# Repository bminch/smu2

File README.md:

# smu2
USB Source Measure Unit Design Files and Source Code

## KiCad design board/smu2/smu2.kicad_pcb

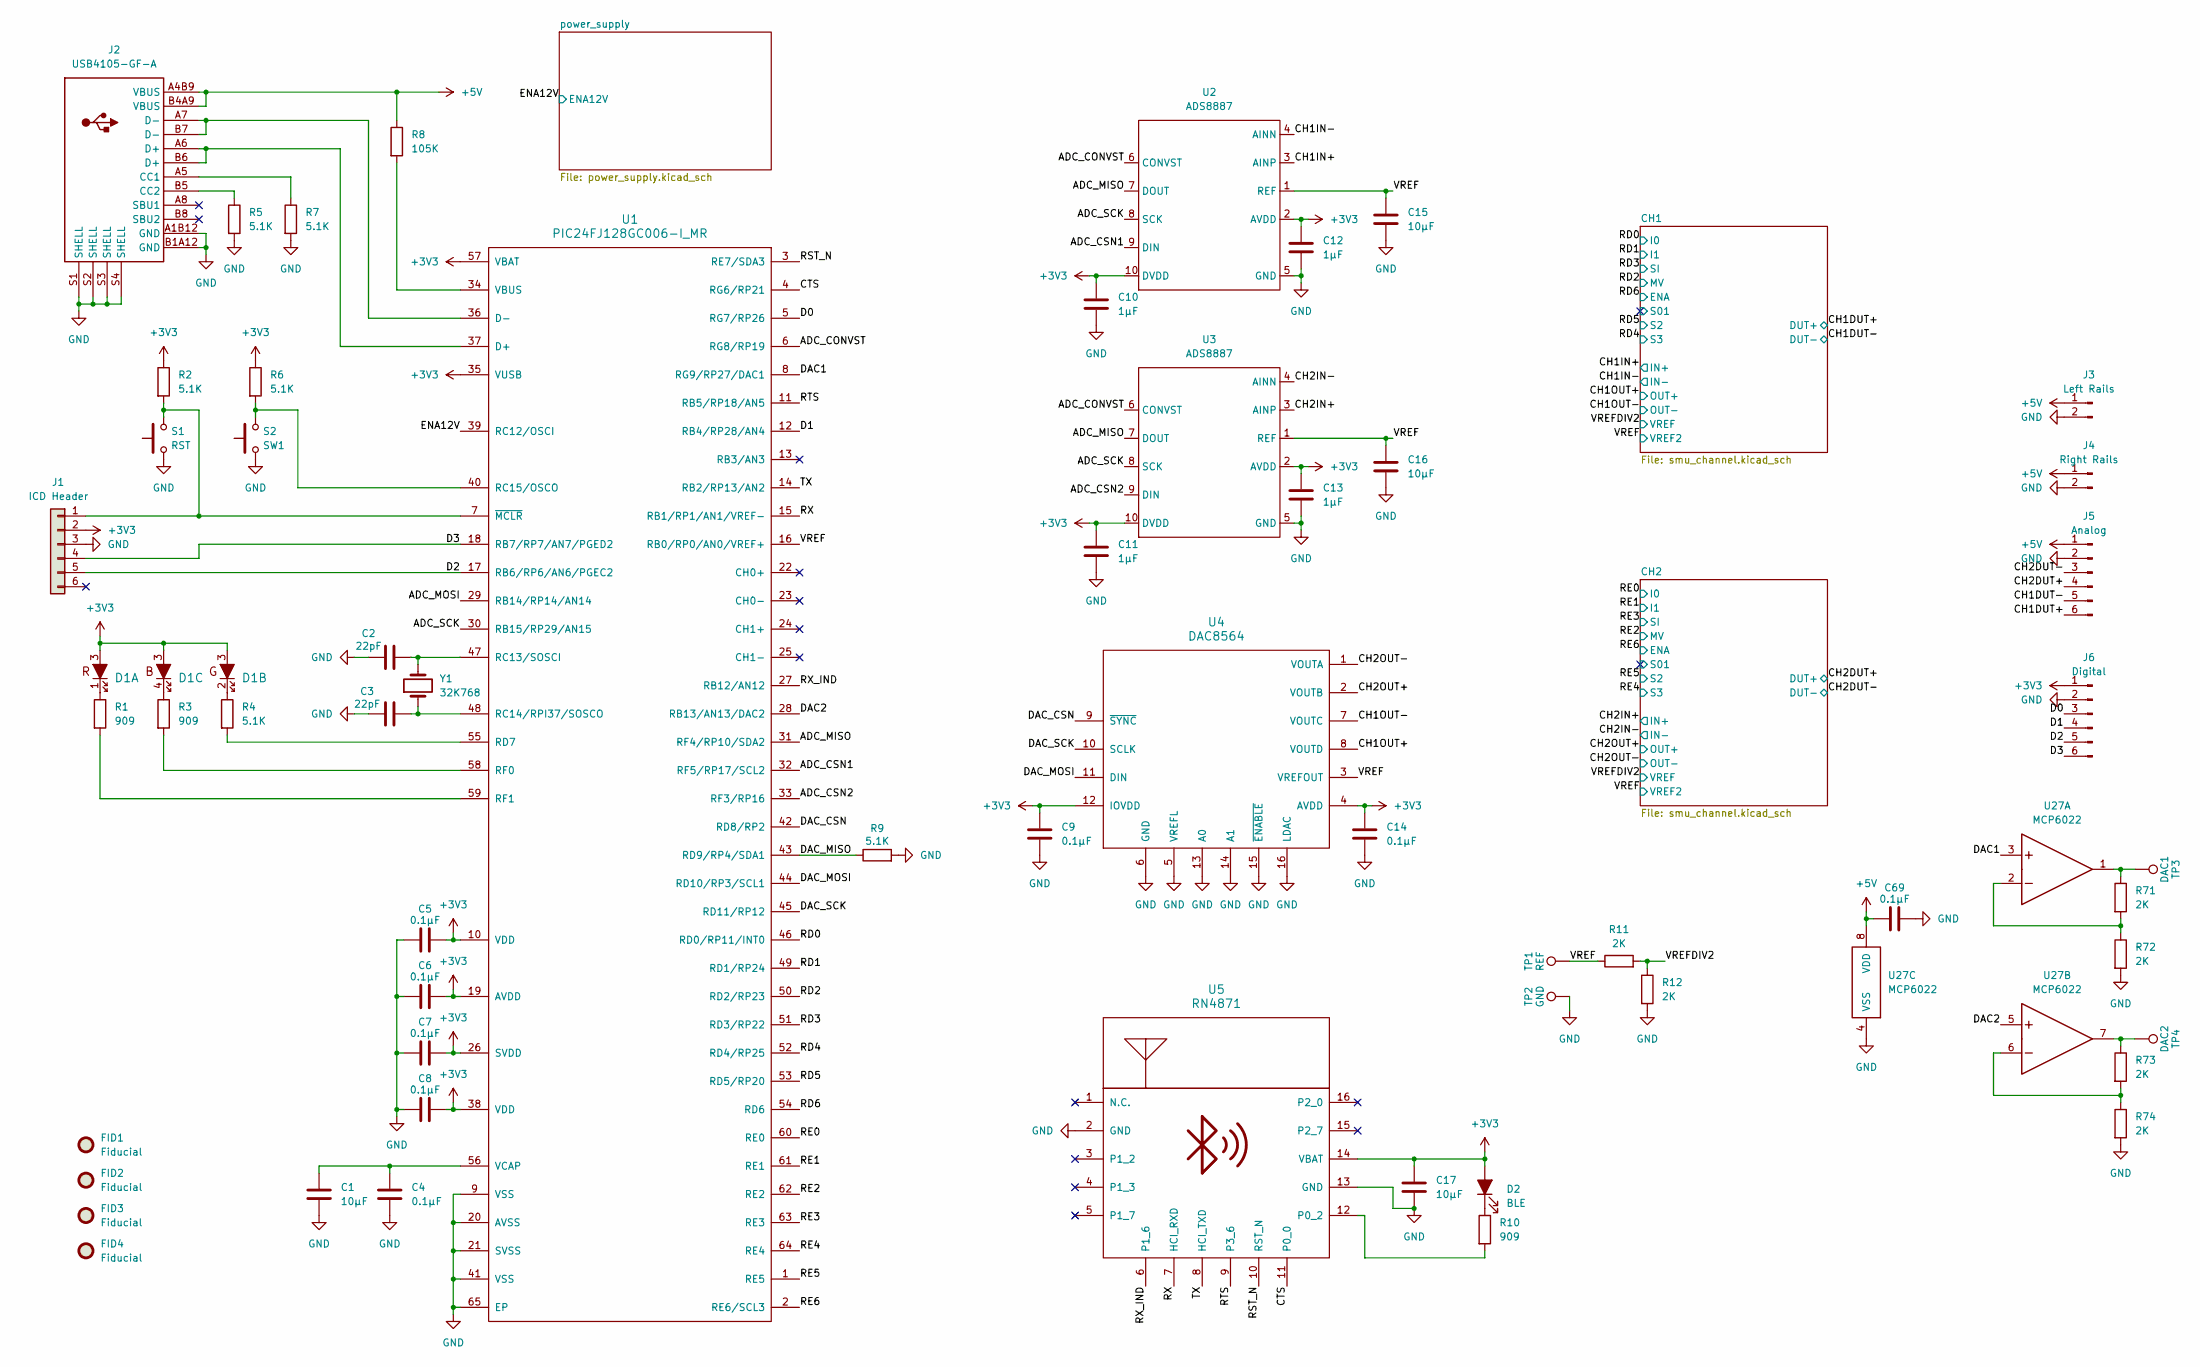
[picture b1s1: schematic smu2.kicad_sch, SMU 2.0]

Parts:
C1, C15, C16, C17: 10µF; C_0603_1608Metric
C2, C3: 22pF; C_0603_1608Metric
C4, C5, C6, C7, C8, C9, C14, C69: 0.1µF; C_0603_1608Metric
C10, C11, C12, C13: 1µF; C_0603_1608Metric
D1: IN-S85TATRGB_ALT; IN-S85TATRGB
D2: BLE; LED_0805_2012Metric
FID1, FID2, FID3, FID4: Fiducial; Fiducial_1mm_Mask2mm
J1: ICD Header; ICD3_header
J2: USB4105-GF-A
J3: Left Rails; PinHeader_1x02_P2.54mm_Vertical
J4: Right Rails; PinHeader_1x02_P2.54mm_Vertical
J5: Analog; PinHeader_1x06_P2.54mm_Vertical
J6: Digital; PinHeader_1x06_P2.54mm_Vertical
R1, R3, R10: 909; R_0603_1608Metric
R2, R4, R5, R6, R7, R9: 5.1K; R_0603_1608Metric
R8: 105K; R_0603_1608Metric
R11, R12, R71, R72, R73, R74: 2K; R_0603_1608Metric
S1: RST; KXT321LHS
S2: SW1; KXT321LHS
TP1: REF; TestPoint_THTPad_D1.5mm_Drill0.7mm
TP2: GND; TestPoint_THTPad_D1.5mm_Drill0.7mm
TP3: DAC1; TestPoint_THTPad_D1.5mm_Drill0.7mm
TP4: DAC2; TestPoint_THTPad_D1.5mm_Drill0.7mm
U1: PIC24FJ128GC006-I_MR; pic24fj128gc006_1
U2, U3: ADS8887; TSSOP-10_3x3mm_P0.5mm
U4: DAC8564; TSSOP-16_4.4x5mm_P0.65mm
U5: RN4871
U27: MCP6022; TSSOP-8_4.4x3mm_P0.65mm
Y1: 32K768; Crystal_SMD_2012-2Pin_2.0x1.2mm

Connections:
+3V3: C5.2, C6.2, C7.2, C8.2, C9.1, C10.1, C11.1, C12.1, C13.1, C14.1, C17.1, D1.3, D2.2 (A), J1.2, J6.1, R2.1, R6.1, U1.10 (VDD), U1.19 (AVDD), U1.26 (SVDD), U1.35 (VUSB), U1.38 (VDD), U1.57 (VBAT), U2.2 (AVDD), U2.10 (DVDD), U3.2 (AVDD), U3.10 (DVDD), U4.4 (AVDD), U4.12 (IOVDD), U5.14 (VBAT); also elsewhere on the board
+5V: C69.1, J2.A4B9 (VBUS), J2.B4A9 (VBUS), J3.1, J4.1, J5.1, R8.1, U27.8 (VDD); also elsewhere on the board
/ADC_CONVST: U1.6 (RG8/RP19), U2.6 (CONVST), U3.6 (CONVST)
/ADC_CSN1: U1.32 (RF5/RP17/SCL2), U2.9 (DIN)
/ADC_CSN2: U1.33 (RF3/RP16), U3.9 (DIN)
/ADC_MISO: U1.31 (RF4/RP10/SDA2), U2.7 (DOUT), U3.7 (DOUT)
/ADC_MOSI: U1.29 (RB14/RP14/AN14)
/ADC_SCK: U1.30 (RB15/RP29/AN15), U2.8 (SCK), U3.8 (SCK)
/CH1DUT+: J5.6; also elsewhere on the board
/CH1DUT-: J5.5; also elsewhere on the board
/CH1IN+: U2.3 (AINP); also elsewhere on the board
/CH1IN-: U2.4 (AINN); also elsewhere on the board
/CH1OUT+: U4.8 (VOUTD); also elsewhere on the board
/CH1OUT-: U4.7 (VOUTC); also elsewhere on the board
/CH2DUT+: J5.4; also elsewhere on the board
/CH2DUT-: J5.3; also elsewhere on the board
/CH2IN+: U3.3 (AINP); also elsewhere on the board
/CH2IN-: U3.4 (AINN); also elsewhere on the board
/CH2OUT+: U4.2 (VOUTB); also elsewhere on the board
/CH2OUT-: U4.1 (VOUTA); also elsewhere on the board
/CTS: U1.4 (RG6/RP21), U5.11 (P0_0)
/D0: J6.3, U1.5 (RG7/RP26)
/D1: J6.4, U1.12 (RB4/RP28/AN4)
/D2: J1.5, J6.5, U1.17 (RB6/RP6/AN6/PGEC2)
/D3: J1.4, J6.6, U1.18 (RB7/RP7/AN7/PGED2)
/DAC1: U1.8 (RG9/RP27/DAC1), U27.3
/DAC2: U1.28 (RB13/AN13/DAC2), U27.5
/DAC_CSN: U1.42 (RD8/RP2), U4.9 (~SYNC)
/DAC_MISO: R9.1, U1.43 (RD9/RP4/SDA1)
/DAC_MOSI: U1.44 (RD10/RP3/SCL1), U4.11 (DIN)
/DAC_SCK: U1.45 (RD11/RP12), U4.10 (SCLK)
/ENA12V: U1.39 (RC12/OSCI); also elsewhere on the board
/RD0: U1.46 (RD0/RP11/INT0); also elsewhere on the board
/RD1: U1.49 (RD1/RP24); also elsewhere on the board
/RD2: U1.50 (RD2/RP23); also elsewhere on the board
/RD3: U1.51 (RD3/RP22); also elsewhere on the board
/RD4: U1.52 (RD4/RP25)
/RD5: U1.53 (RD5/RP20); also elsewhere on the board
/RD6: U1.54 (RD6); also elsewhere on the board
/RE0: U1.60 (RE0); also elsewhere on the board
/RE1: U1.61 (RE1); also elsewhere on the board
/RE2: U1.62 (RE2); also elsewhere on the board
/RE3: U1.63 (RE3); also elsewhere on the board
/RE4: U1.64 (RE4)
/RE5: U1.1 (RE5); also elsewhere on the board
/RE6: U1.2 (RE6/SCL3); also elsewhere on the board
/RST_N: U1.3 (RE7/SDA3), U5.10 (RST_N)
/RTS: U1.11 (RB5/RP18/AN5), U5.9 (P3_6)
/RX: U1.15 (RB1/RP1/AN1/VREF-), U5.7 (HCI_RXD)
/RX_IND: U1.27 (RB12/AN12), U5.6 (P1_6)
/TX: U1.14 (RB2/RP13/AN2), U5.8 (HCI_TXD)
/VREF: C15.1, C16.1, R11.1, TP1.1, U1.16 (RB0/RP0/AN0/VREF+), U2.1 (REF), U3.1 (REF), U4.3 (VREFOUT); also elsewhere on the board
/VREFDIV2: R11.2, R12.1; also elsewhere on the board
GND: C1.2, C2.1, C3.1, C4.2, C5.1, C6.1, C7.1, C8.1, C9.2, C10.2, C11.2, C12.2, C13.2, C14.2, C15.2, C16.2, C17.2, C69.2, J1.3, J2.A1B12 (GND), J2.B1A12 (GND), J2.S1 (SHELL), J2.S2 (SHELL), J2.S3 (SHELL), J2.S4 (SHELL), J3.2, J4.2, J5.2, J6.2, R5.2, R7.2, R9.2, R12.2, R72.2, R74.2, S1.1, S2.1, TP2.1, U1.9 (VSS), U1.20 (AVSS), U1.21 (SVSS), U1.41 (VSS), U1.65 (EP), U2.5 (GND), U3.5 (GND), U4.5 (VREFL), U4.6 (GND), U4.13 (A0), U4.14 (A1), U4.15 (~ENABLE), U4.16 (LDAC), U5.2 (GND), U5.13 (GND), U27.4 (VSS); also elsewhere on the board
unnamed: D1.1, R1.1
unnamed: D1.2, R4.1
unnamed: D1.4, R3.1
unnamed: D2.1 (K), R10.1
unnamed: J1.1, R2.2, S1.2, U1.7 (~MCLR)
unnamed: J2.A5 (CC1), R7.1
unnamed: J2.B5 (CC2), R5.1
unnamed: R71.1, TP3.1, U27.1
unnamed: R71.2, R72.1, U27.2
unnamed: R73.1, TP4.1, U27.7
unnamed: R73.2, R74.1, U27.6
unnamed: J2.A6 (D+), J2.B6 (D+), U1.37 (D+)
unnamed: J2.A7 (D-), J2.B7 (D-), U1.36 (D-)
unnamed: C2.2, U1.47 (RC13/SOSCI), Y1.2
unnamed: C3.2, U1.48 (RC14/RPI37/SOSCO), Y1.1
unnamed: R6.2, S2.2, U1.40 (RC15/OSCO)
unnamed: R4.2, U1.55 (RD7)
unnamed: R3.2, U1.58 (RF0)
unnamed: R1.2, U1.59 (RF1)
unnamed: R8.2, U1.34 (VBUS)
unnamed: C1.1, C4.1, U1.56 (VCAP)
unnamed: R10.2, U5.12 (P0_2)

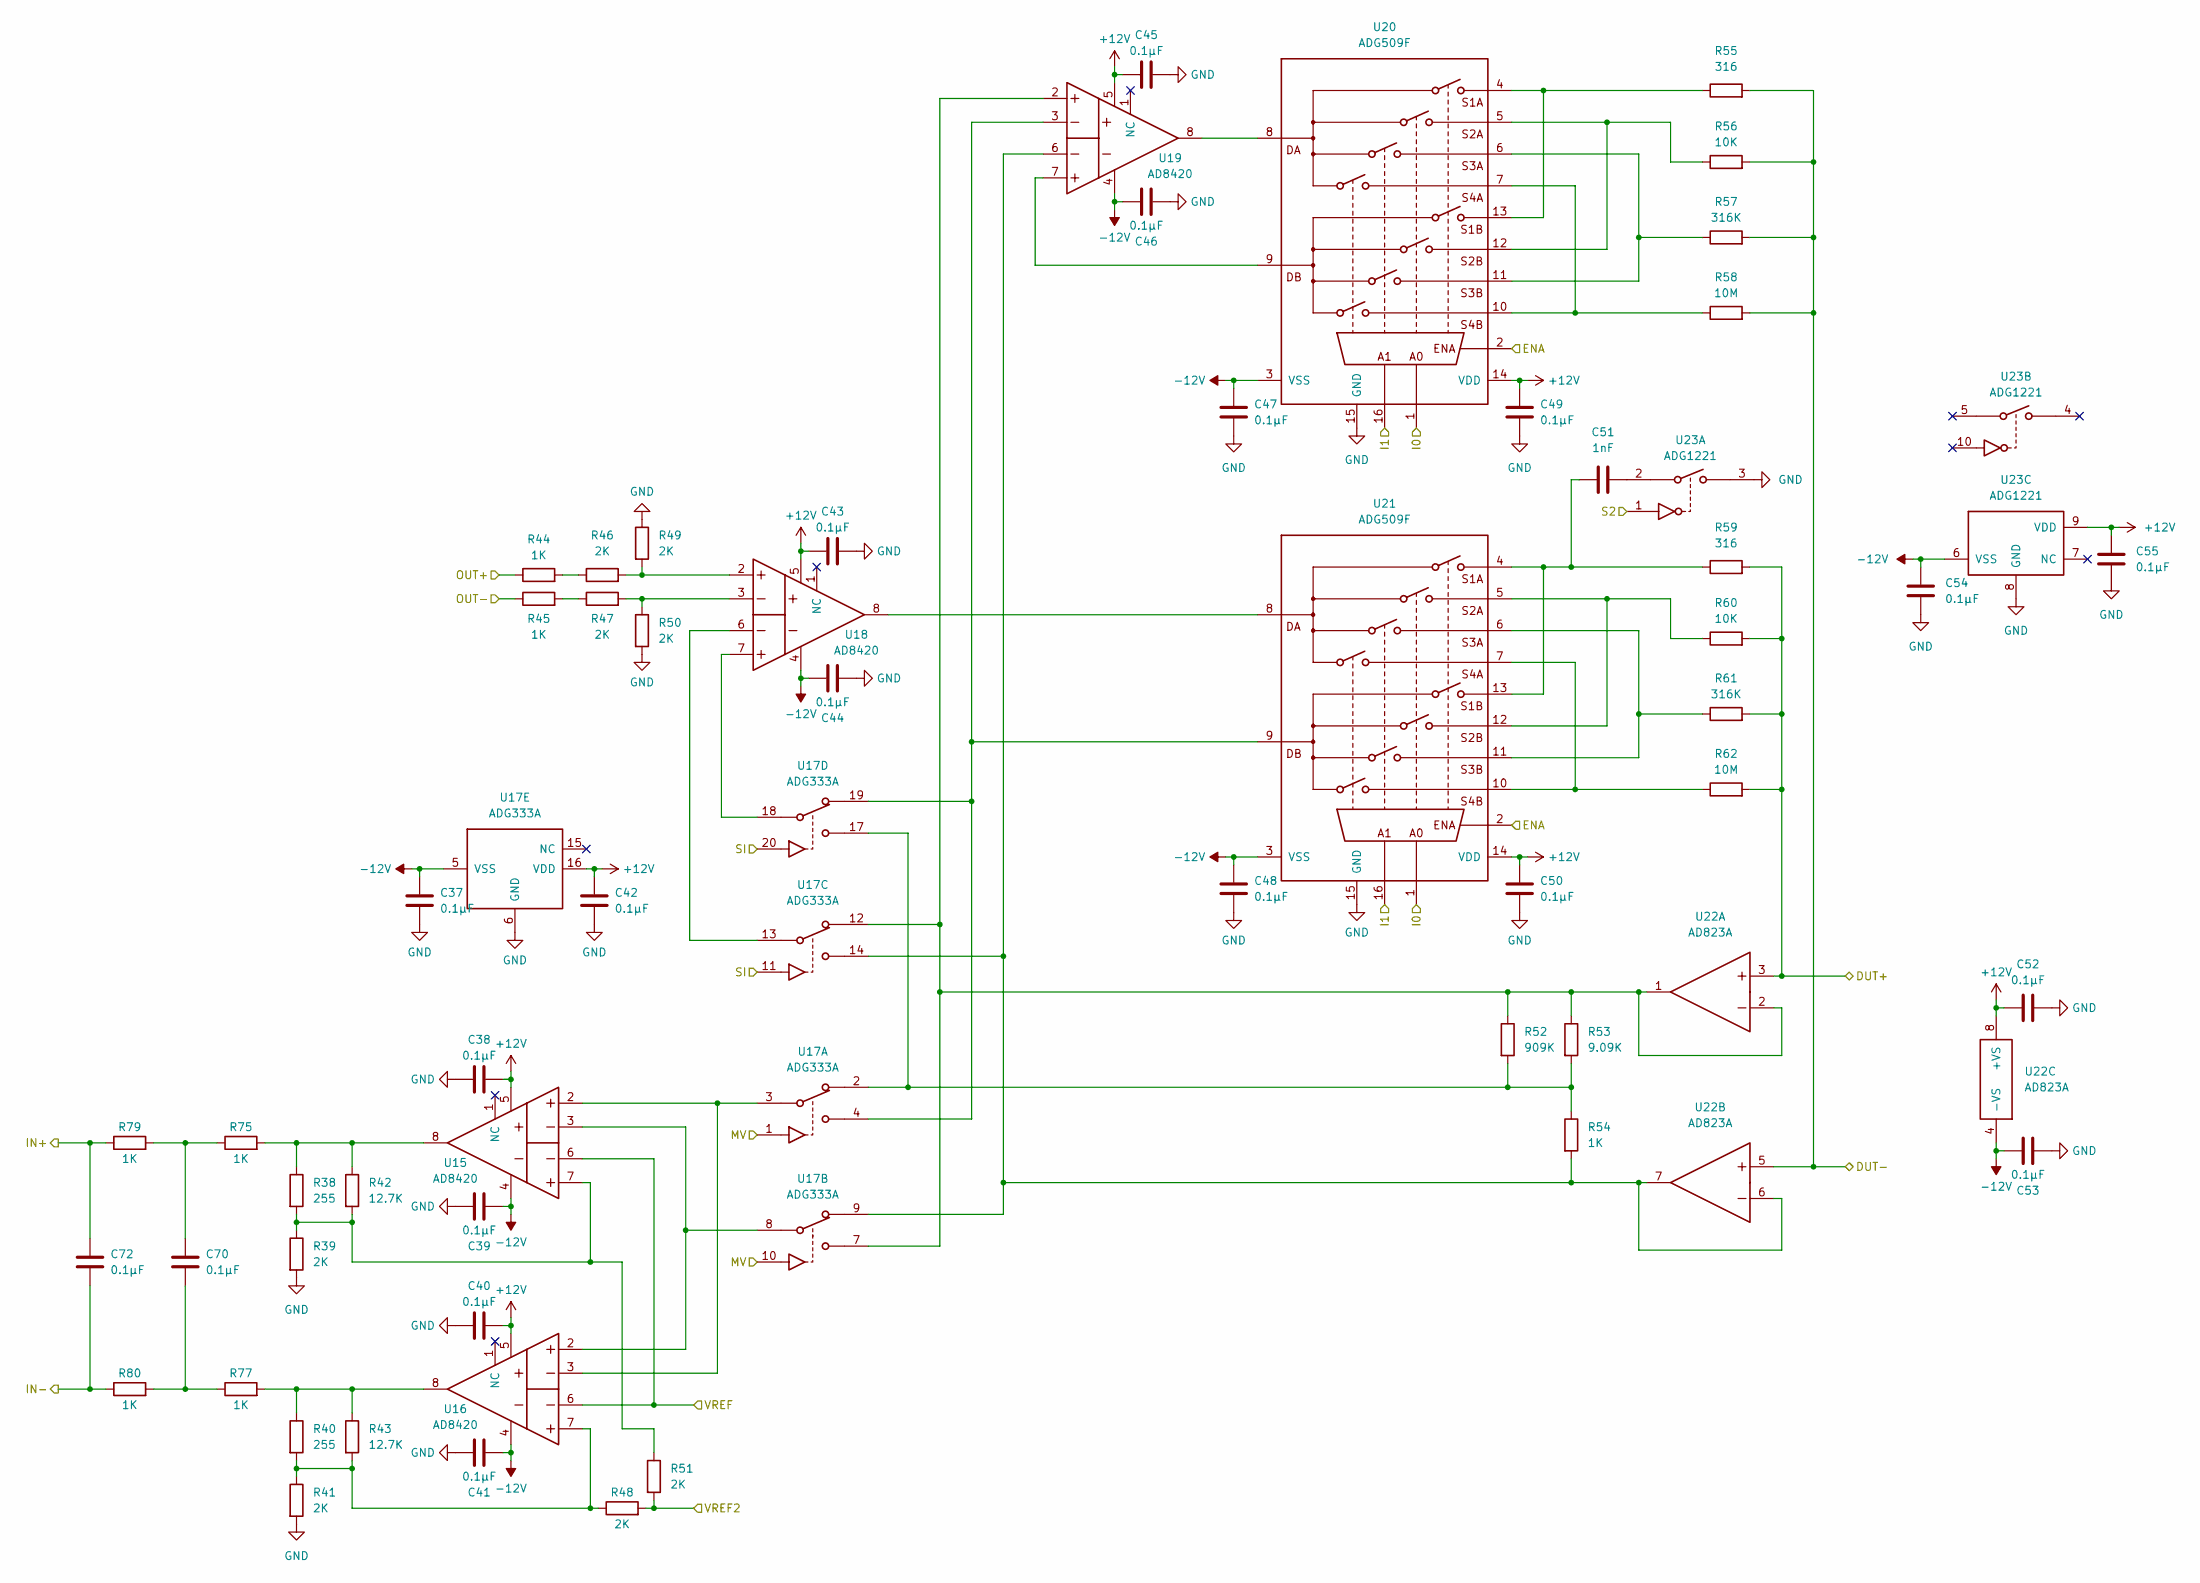
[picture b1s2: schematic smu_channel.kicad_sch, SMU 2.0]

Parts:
C37, C38, C39, C40, C41, C42, C43, C44, C45, C46, C47, C48, C49, C50, C52, C53, C54, C55, C70, C72: 0.1µF; C_0603_1608Metric
C51: 1nF; C_0603_1608Metric
R38, R40: 255; R_0603_1608Metric
R39, R41, R46, R47, R48, R49, R50, R51: 2K; R_0603_1608Metric
R42, R43: 12.7K; R_0603_1608Metric
R44, R45, R54, R75, R77, R79, R80: 1K; R_0603_1608Metric
R52: 909K; R_0603_1608Metric
R53: 9.09K; R_0603_1608Metric
R55, R59: 316; R_0603_1608Metric
R56, R60: 10K; R_0603_1608Metric
R57, R61: 316K; R_0603_1608Metric
R58, R62: 10M; R_1206_3216Metric
U15, U16, U18, U19: AD8420; MSOP-8_3x3mm_P0.65mm
U17: ADG333A; SSOP-20_5.3x7.2mm_P0.65mm
U20, U21: ADG509F; TSSOP-16_4.4x5mm_P0.65mm
U22: AD823A; MSOP-8_3x3mm_P0.65mm
U23: ADG1221; MSOP-10_3x3mm_P0.5mm

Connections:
+12V: C38.2, C40.2, C42.1, C43.1, C45.1, C49.1, C50.1, C52.1, C55.1, U15.5, U16.5, U17.16 (VDD), U18.5, U19.5, U20.14 (VDD), U21.14 (VDD), U22.8 (+VS), U23.9 (VDD); also elsewhere on the board
-12V: C37.1, C39.2, C41.2, C44.1, C46.1, C47.1, C48.1, C53.1, C54.1, U15.4, U16.4, U17.5 (VSS), U18.4, U19.4, U20.3 (VSS), U21.3 (VSS), U22.4 (-VS), U23.6 (VSS); also elsewhere on the board
/CH1IN+: C72.1, R79.1; also elsewhere on the board
/CH1IN-: C72.2, R80.1; also elsewhere on the board
/CH2DUT+: R59.2, R60.2, R61.2, R62.2, U22.3; also elsewhere on the board
/CH2DUT-: R55.2, R56.2, R57.2, R58.2, U22.5; also elsewhere on the board
/CH2OUT+: R44.1; also elsewhere on the board
/CH2OUT-: R45.1; also elsewhere on the board
/RE0: U20.1, U21.1; also elsewhere on the board
/RE1: U20.16, U21.16; also elsewhere on the board
/RE2: U17.1, U17.10; also elsewhere on the board
/RE3: U17.11, U17.20; also elsewhere on the board
/RE5: U23.1; also elsewhere on the board
/RE6: U20.2, U21.2; also elsewhere on the board
/VREF: R48.2, R51.2; also elsewhere on the board
/VREFDIV2: U15.6, U16.6; also elsewhere on the board
GND: C37.2, C38.1, C39.1, C40.1, C41.1, C42.2, C43.2, C44.2, C45.2, C46.2, C47.2, C48.2, C49.2, C50.2, C52.2, C53.2, C54.2, C55.2, R39.2, R41.2, R49.1, R50.2, U17.6 (GND), U20.15 (GND), U21.15 (GND), U23.3, U23.8 (GND); also elsewhere on the board
unnamed: C51.1, R59.1, U21.4, U21.13
unnamed: C51.2, U23.2
unnamed: C70.1, R75.1, R79.2
unnamed: C70.2, R77.1, R80.2
unnamed: R38.2, R39.1, R42.2, R51.1, U15.7
unnamed: R40.2, R41.1, R43.2, R48.1, U16.7
unnamed: R44.2, R46.1
unnamed: R45.2, R47.1
unnamed: R46.2, R49.2, U18.2
unnamed: R47.2, R50.1, U18.3
unnamed: R52.1, R53.1, U17.7, U17.12, U19.2, U22.1, U22.2
unnamed: R52.2, R53.2, R54.1, U17.2, U17.17
unnamed: R54.2, U17.9, U17.14, U19.6, U22.6, U22.7
unnamed: R55.1, U20.4, U20.13
unnamed: R56.1, U20.5, U20.12
unnamed: R57.1, U20.6, U20.11
unnamed: R58.1, U20.7, U20.10
unnamed: R60.1, U21.5, U21.12
unnamed: R61.1, U21.6, U21.11
unnamed: R62.1, U21.7, U21.10
unnamed: U15.2, U16.3, U17.3
unnamed: U15.3, U16.2, U17.8
unnamed: U17.13, U18.6
unnamed: U17.18, U18.7
unnamed: U17.4, U17.19, U19.3, U21.9
unnamed: U18.8, U21.8
unnamed: U19.7, U20.9
unnamed: U19.8, U20.8

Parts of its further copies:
C18, C19, C20, C21, C22, C23, C24, C25, C26, C27, C28, C29, C30, C31, C33, C34, C35, C36, C71, C73: 0.1µF; C_0603_1608Metric
C32: 1nF; C_0603_1608Metric
R13, R15: 255; R_0603_1608Metric
R14, R16, R21, R22, R23, R24, R25, R26: 2K; R_0603_1608Metric
R17, R18: 12.7K; R_0603_1608Metric
R19, R20, R29, R76, R78, R81, R82: 1K; R_0603_1608Metric
R27: 909K; R_0603_1608Metric
R28: 9.09K; R_0603_1608Metric
R30, R34: 316; R_0603_1608Metric
R31, R35: 10K; R_0603_1608Metric
R32, R36: 316K; R_0603_1608Metric
R33, R37: 10M; R_1206_3216Metric
U6, U7, U9, U10: AD8420; MSOP-8_3x3mm_P0.65mm
U8: ADG333A; SSOP-20_5.3x7.2mm_P0.65mm
U11, U12: ADG509F; TSSOP-16_4.4x5mm_P0.65mm
U13: AD823A; MSOP-8_3x3mm_P0.65mm
U14: ADG1221; MSOP-10_3x3mm_P0.5mm

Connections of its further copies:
+12V: C19.2, C21.2, C23.1, C24.1, C26.1, C30.1, C31.1, C33.1, C36.1, U6.5, U7.5, U8.16 (VDD), U9.5, U10.5, U11.14 (VDD), U12.14 (VDD), U13.8 (+VS), U14.9 (VDD); also elsewhere on the board
-12V: C18.1, C20.2, C22.2, C25.1, C27.1, C28.1, C29.1, C34.1, C35.1, U6.4, U7.4, U8.5 (VSS), U9.4, U10.4, U11.3 (VSS), U12.3 (VSS), U13.4 (-VS), U14.6 (VSS); also elsewhere on the board
/CH1DUT+: R34.2, R35.2, R36.2, R37.2, U13.3; also elsewhere on the board
/CH1DUT-: R30.2, R31.2, R32.2, R33.2, U13.5; also elsewhere on the board
/CH1OUT+: R19.1; also elsewhere on the board
/CH1OUT-: R20.1; also elsewhere on the board
/CH2IN+: C73.1, R81.1; also elsewhere on the board
/CH2IN-: C73.2, R82.1; also elsewhere on the board
/RD0: U11.1, U12.1; also elsewhere on the board
/RD1: U11.16, U12.16; also elsewhere on the board
/RD2: U8.1, U8.10; also elsewhere on the board
/RD3: U8.11, U8.20; also elsewhere on the board
/RD5: U14.1; also elsewhere on the board
/RD6: U11.2, U12.2; also elsewhere on the board
/VREF: R23.2, R26.2; also elsewhere on the board
/VREFDIV2: U6.6, U7.6; also elsewhere on the board
GND: C18.2, C19.1, C20.1, C21.1, C22.1, C23.2, C24.2, C25.2, C26.2, C27.2, C28.2, C29.2, C30.2, C31.2, C33.2, C34.2, C35.2, C36.2, R14.2, R16.2, R24.1, R25.2, U8.6 (GND), U11.15 (GND), U12.15 (GND), U14.3, U14.8 (GND); also elsewhere on the board
unnamed: C32.1, R34.1, U12.4, U12.13
unnamed: C32.2, U14.2
unnamed: C71.1, R76.1, R81.2
unnamed: C71.2, R78.1, R82.2
unnamed: R13.2, R14.1, R17.2, R26.1, U6.7
unnamed: R15.2, R16.1, R18.2, R23.1, U7.7
unnamed: R19.2, R21.1
unnamed: R20.2, R22.1
unnamed: R21.2, R24.2, U9.2
unnamed: R22.2, R25.1, U9.3
unnamed: R27.1, R28.1, U8.7, U8.12, U10.2, U13.1, U13.2
unnamed: R27.2, R28.2, R29.1, U8.2, U8.17
unnamed: R29.2, U8.9, U8.14, U10.6, U13.6, U13.7
unnamed: R30.1, U11.4, U11.13
unnamed: R31.1, U11.5, U11.12
unnamed: R32.1, U11.6, U11.11
unnamed: R33.1, U11.7, U11.10
unnamed: R35.1, U12.5, U12.12
unnamed: R36.1, U12.6, U12.11
unnamed: R37.1, U12.7, U12.10
unnamed: U6.2, U7.3, U8.3
unnamed: U6.3, U7.2, U8.8
unnamed: U8.13, U9.6
unnamed: U8.18, U9.7
unnamed: U8.4, U8.19, U10.3, U12.9
unnamed: U10.7, U11.9
unnamed: U10.8, U11.8
unnamed: U9.8, U12.8

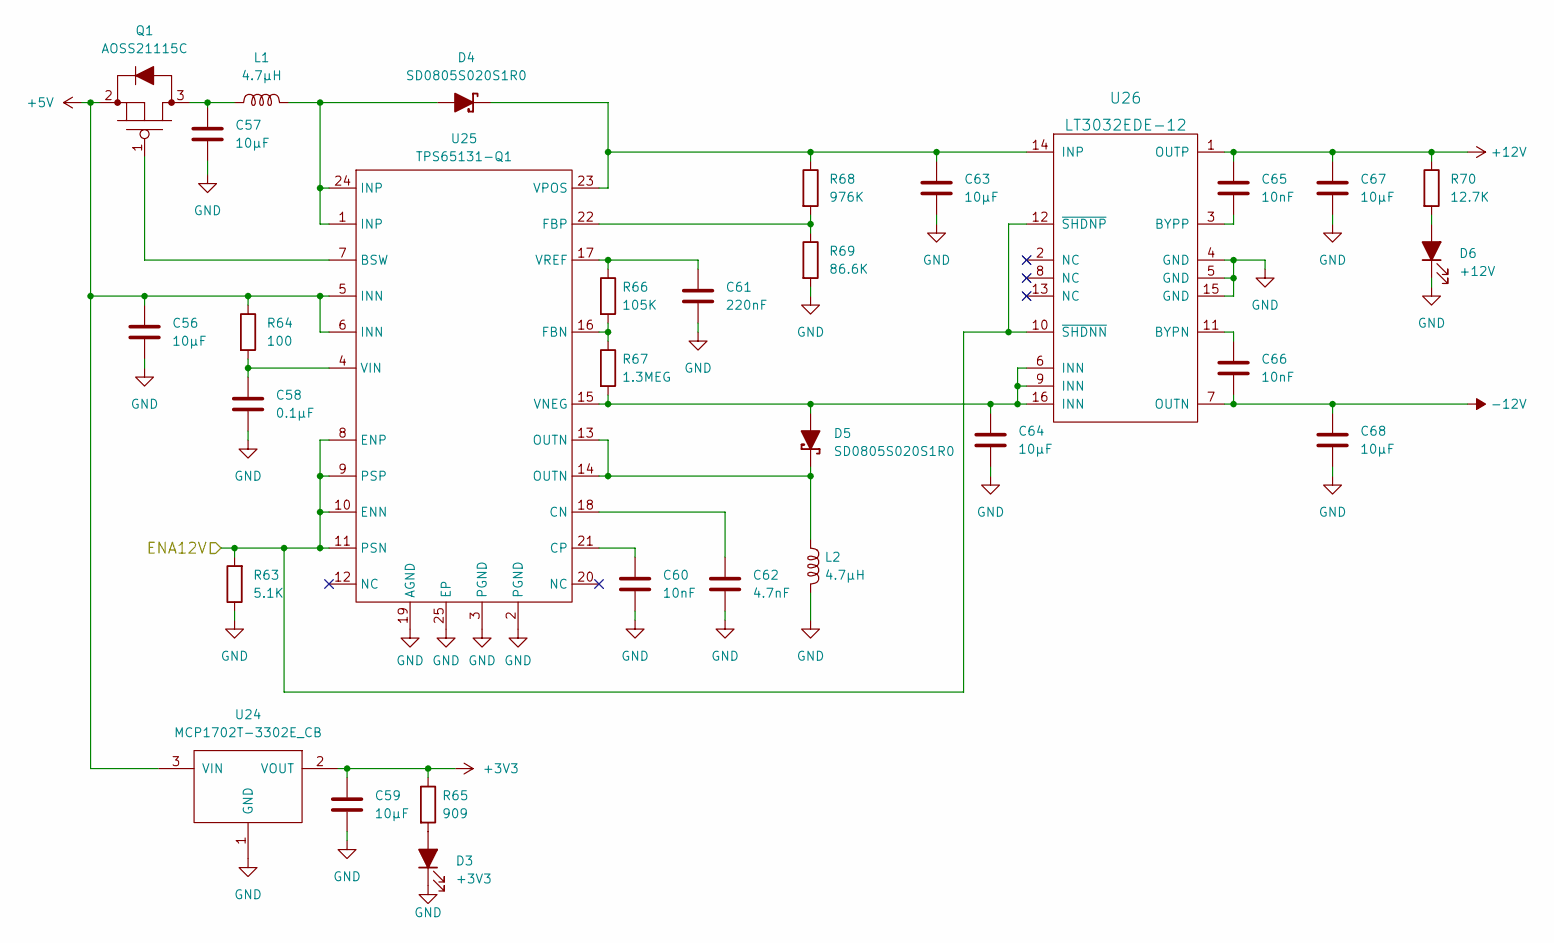
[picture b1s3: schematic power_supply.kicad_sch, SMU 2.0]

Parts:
C56, C57, C59, C63, C64, C67, C68: 10µF; C_0603_1608Metric
C58: 0.1µF; C_0603_1608Metric
C60, C65, C66: 10nF; C_0603_1608Metric
C61: 220nF; C_0603_1608Metric
C62: 4.7nF; C_0603_1608Metric
D3: +3V3; LED_0805_2012Metric
D4, D5: SD0805S020S1R0; D_0805_2012Metric
D6: +12V; LED_0805_2012Metric
L1, L2: 4.7µH; PA5003.182NLT
Q1: AOSS21115C; SOT-23
R63: 5.1K; R_0603_1608Metric
R64: 100; R_0603_1608Metric
R65: 909; R_0603_1608Metric
R66: 105K; R_0603_1608Metric
R67: 1.3MEG; R_0603_1608Metric
R68: 976K; R_0603_1608Metric
R69: 86.6K; R_0603_1608Metric
R70: 12.7K; R_0603_1608Metric
U24: MCP1702T-3302E_CB; SOT-23
U25: TPS65131-Q1; TPS65131-Q_1
U26: LT3032EDE-12; LT3032_1

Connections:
+3V3: C59.1, R65.1, U24.2 (VOUT); also elsewhere on the board
+5V: C56.1, Q1.2, R64.1, U24.3 (VIN), U25.5 (INN), U25.6 (INN); also elsewhere on the board
+12V: C65.1, C67.1, R70.1, U26.1 (OUTP); also elsewhere on the board
-12V: C66.2, C68.1, U26.7 (OUTN); also elsewhere on the board
/ENA12V: R63.2, U25.8 (ENP), U25.9 (PSP), U25.10 (ENN), U25.11 (PSN), U26.10 (~SHDNN), U26.12 (~SHDNP); also elsewhere on the board
GND: C56.2, C57.2, C58.2, C59.2, C60.2, C61.2, C62.2, C63.2, C64.2, C67.2, C68.2, D3.1 (K), D6.1 (K), L2.2, R63.1, R69.2, U24.1 (GND), U25.2 (PGND), U25.3 (PGND), U25.19 (AGND), U25.25 (EP), U26.4 (GND), U26.5 (GND), U26.15 (GND); also elsewhere on the board
unnamed: C57.1, L1.1, Q1.3
unnamed: D3.2 (A), R65.2
unnamed: D4.2, L1.2, U25.1 (INP), U25.24 (INP)
unnamed: D5.1, L2.1, U25.13 (OUTN), U25.14 (OUTN)
unnamed: D6.2 (A), R70.2
unnamed: Q1.1, U25.7 (BSW)
unnamed: C62.1, U25.18 (CN)
unnamed: C60.1, U25.21 (CP)
unnamed: R66.2, R67.1, U25.16 (FBN)
unnamed: R68.2, R69.1, U25.22 (FBP)
unnamed: C58.1, R64.2, U25.4 (VIN)
unnamed: C64.1, D5.2, R67.2, U25.15 (VNEG), U26.6 (INN), U26.9 (INN), U26.16 (INN)
unnamed: C63.1, D4.1, R68.1, U25.23 (VPOS), U26.14 (INP)
unnamed: C61.1, R66.1, U25.17 (VREF)
unnamed: C66.1, U26.11 (BYPN)
unnamed: C65.2, U26.3 (BYPP)

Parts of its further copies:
C22: 0.1µF; C_0603_1608Metric

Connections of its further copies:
-12V: C22.2; also elsewhere on the board
GND: C22.1; also elsewhere on the board

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
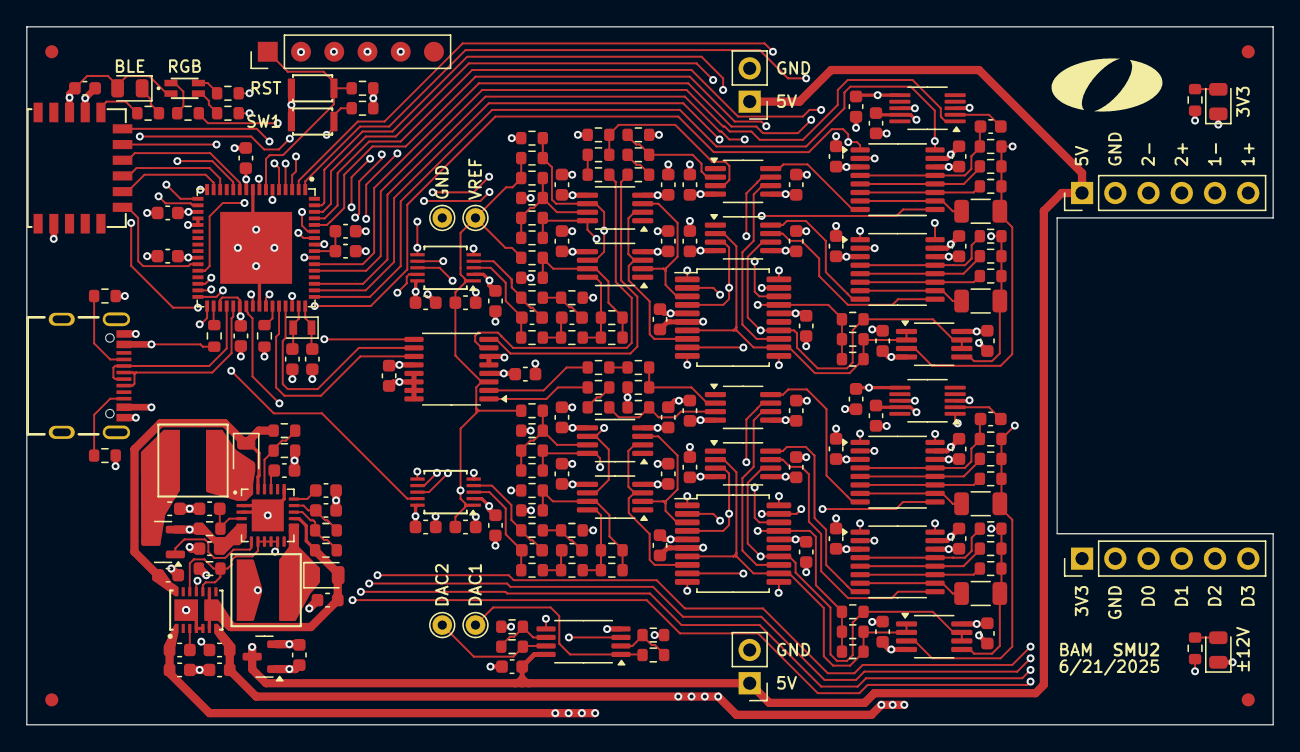
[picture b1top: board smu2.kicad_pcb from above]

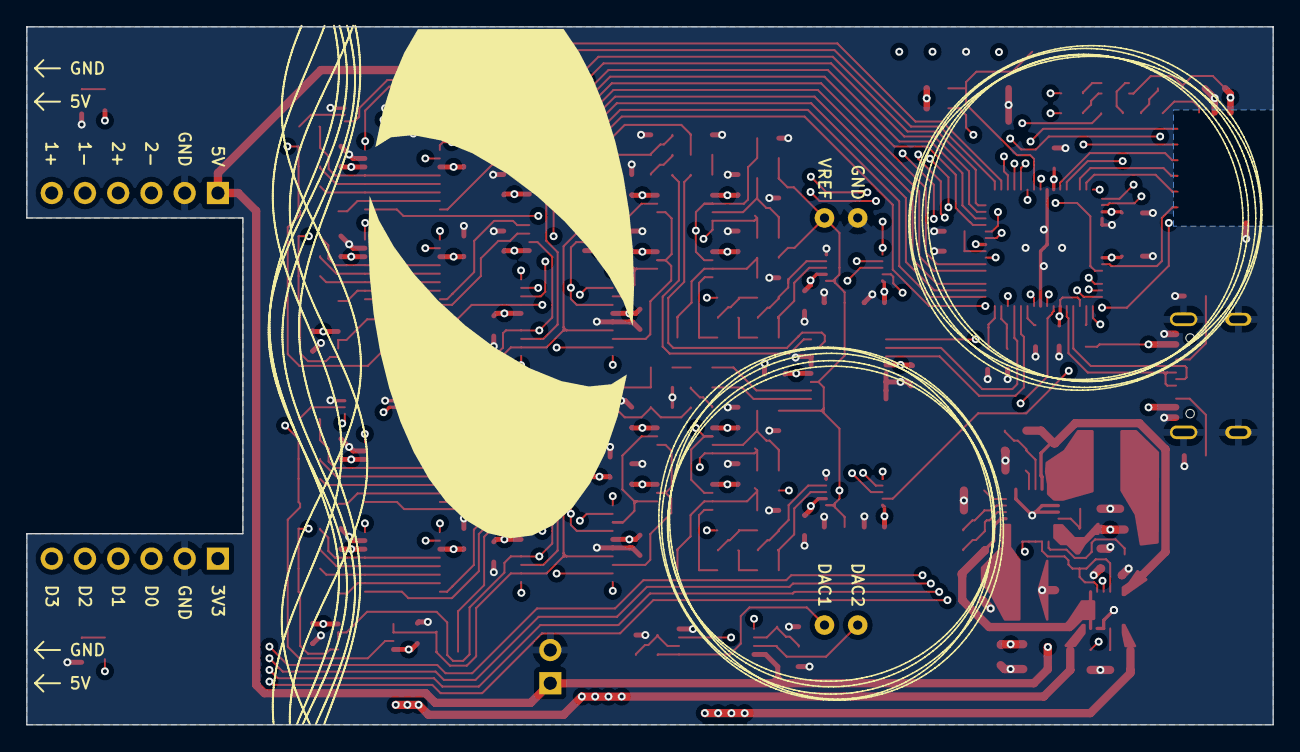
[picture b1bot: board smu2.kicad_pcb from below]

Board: 4 copper layers, 95.2 x 53.3 mm, 212 parts (3 on the bottom side), 151 nets.

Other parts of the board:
OlinLogoLg1: G***; OlinLogoLg1
OlinLogoTruncated: G***; OlinLogoTruncated
svg2mod, svg2mod#2: G***; gesture_ellipse

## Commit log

2025-06-17 Add board files.
2025-06-17 Removed some extraneous files.
2025-06-17 Added firmware and software source code.
2025-06-20 Changed R4 from 909Ω to 5.1kΩ
2025-06-26 Updated PCB design files.
2025-06-26 Updated interactive BoM and PDF schematic.
2025-06-26 Updated BoM and parts sheet.
2025-07-09 Added commands and methods to get SMU state for a virtual display.
